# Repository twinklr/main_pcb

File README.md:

# Twinklr Main Board

This repository contains layouts for the Twinklr main PCB in EAGLE's `brd` and `sch` formats. Gerber files are also included.

## `twinklr_board`

This was the original Twinklr board with a built-in 1W amplifier. Unfortunately, it doesn't really work very well, so the amplifier was removed from the final version.

## `twinklr_board_5v`

This is the board used in the current version of Twinklr. It distributes 5V from a tip-negative PSU to the Raspberry Pi, rather than stepping down 9V with a regulator. It has no amplifier.

## License  

Twinklr is Open Hardware.

<br /><span
xmlns:dct="http://purl.org/dc/terms/" property="dct:title">Twinklr</span> by
<span xmlns:cc="http://creativecommons.org/ns#"
property="cc:attributionName">Tom Armitage and Richard Birkin</span> is Open
Hardware. It is licensed under a <a rel="license"
href="http://creativecommons.org/licenses/by-sa/4.0/">Creative Commons
Attribution-ShareAlike 4.0 International License</a>  
If you use any work in this project, you should credit us, and you must
republish any changes you make under the same license. This license does permit
commercial use of these designs, but consider getting in touch before selling
anything.

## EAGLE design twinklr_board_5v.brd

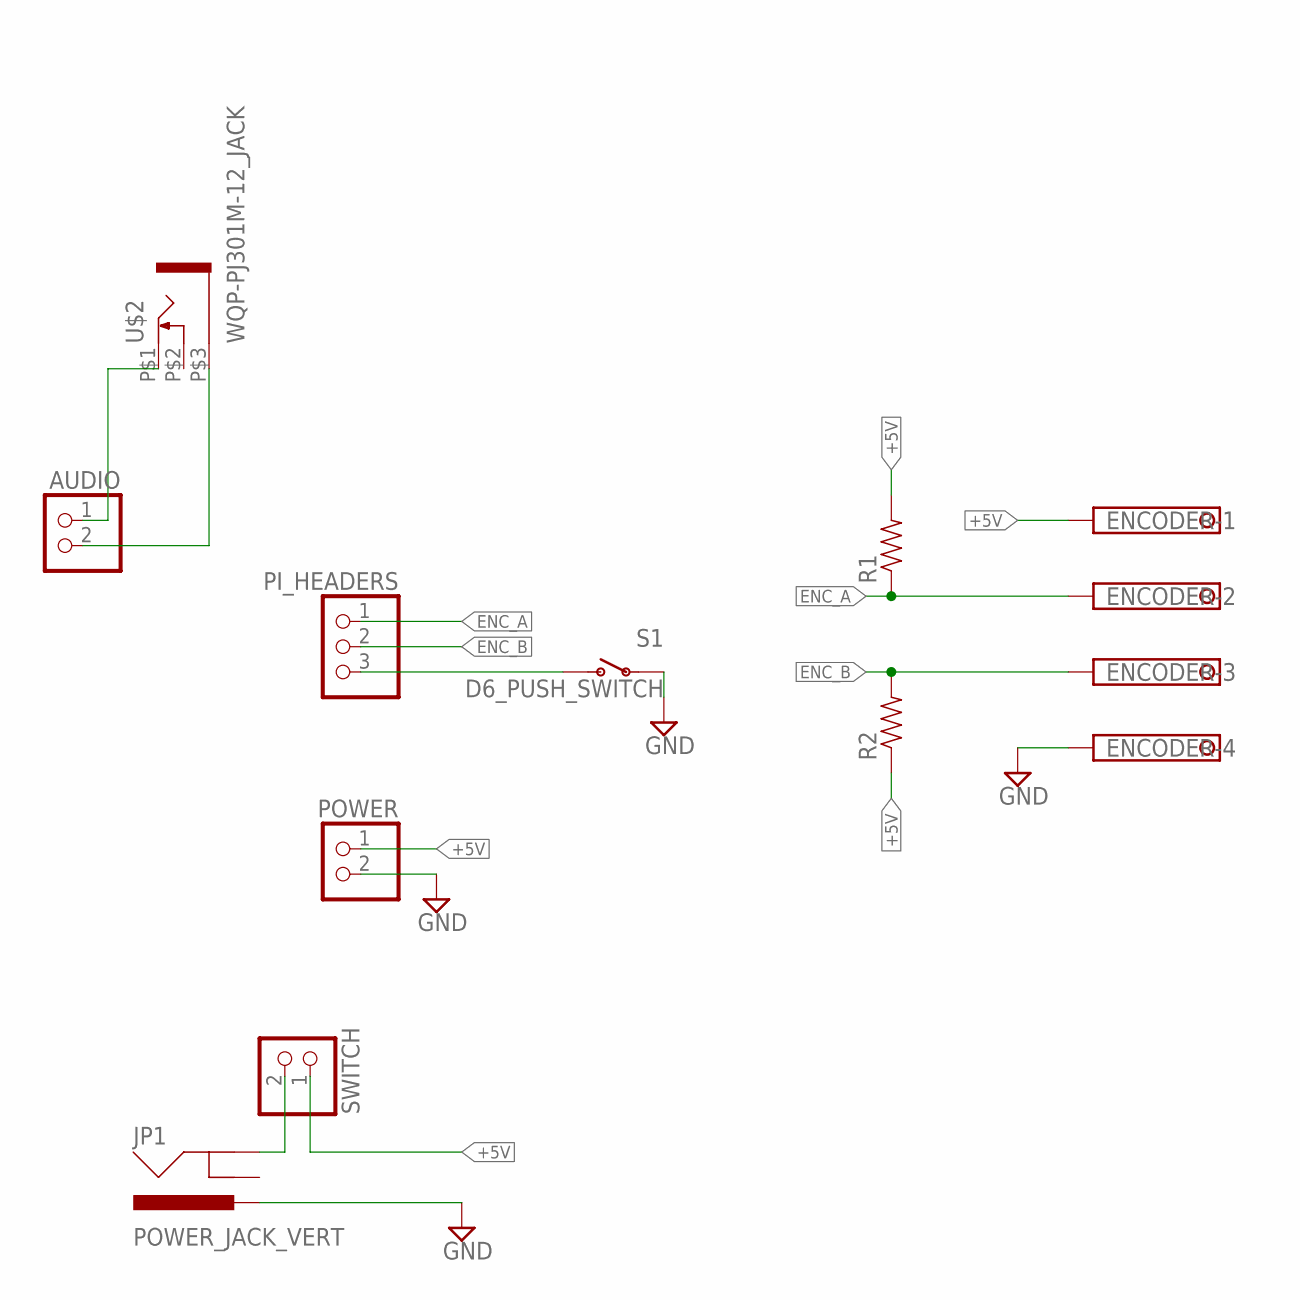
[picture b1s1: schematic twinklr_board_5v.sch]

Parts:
AUDIO: PINHD-1X2; 1X02
ENCODER: 1751264
JP1: POWER_JACK_VERT
PI_HEADERS: PINHD-1X3; 1X03
POWER: PINHD-1X2; 1X02
R1, R2: RESISTORAXIAL-0.3; AXIAL-0.3
S1: D6_PUSH_SWITCH
SWITCH: PINHD-1X2; 1X02
U$2: WQP-PJ301M-12_JACK

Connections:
+5V: ENCODER.1, POWER.1, R1.P$2 (2), R2.P$1 (1), SWITCH.1
ENC_A: ENCODER.2, PI_HEADERS.1, R1.P$1 (1)
ENC_B: ENCODER.3, PI_HEADERS.2, R2.P$2 (2)
GND: ENCODER.4, JP1.PWR, POWER.2, S1.P$3, S1.P$4
unnamed: AUDIO.2, U$2.P$3 (1)
unnamed: AUDIO.1, U$2.P$1 (2)
unnamed: JP1.GND, SWITCH.2
unnamed: PI_HEADERS.3, S1.P$1 (O), S1.P$2 (O)

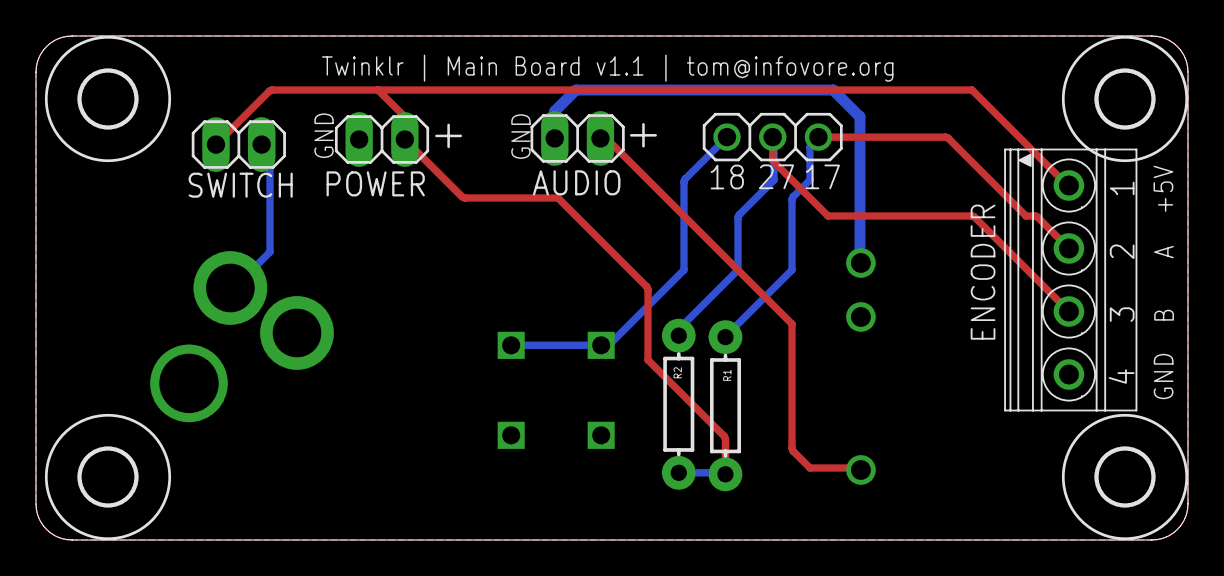
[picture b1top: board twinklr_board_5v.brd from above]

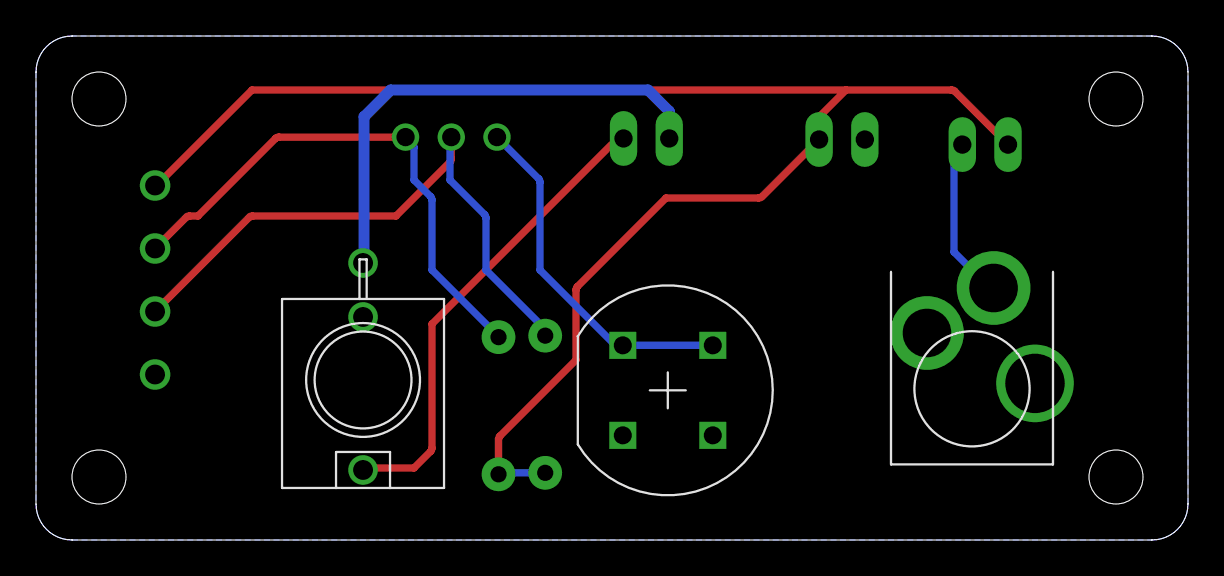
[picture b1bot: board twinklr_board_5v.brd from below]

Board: 2 copper layers, 64.0 x 28.0 mm, 14 parts (3 on the bottom side), 8 nets.

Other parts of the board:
U$1, U$3, U$4, U$5: 3,0

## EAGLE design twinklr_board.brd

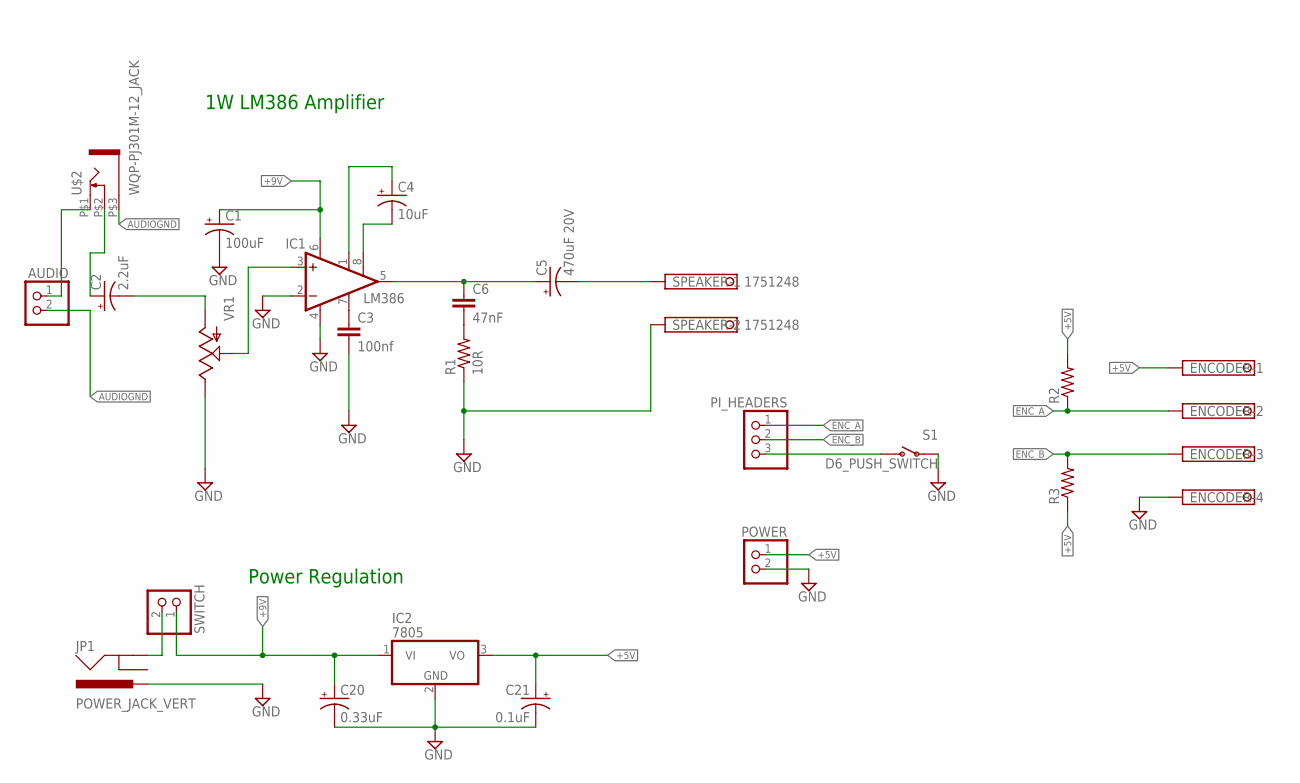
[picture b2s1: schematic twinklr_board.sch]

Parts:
AUDIO: PINHD-1X2; 1X02
C1: 100uF; CPOL-RADIAL-10UF-25V
C2: 2.2uF; CPOL-RADIAL-10UF-25V
C3: 100nf; CAP-PTH-SMALL
C4: 10uF; CPOL-RADIAL-10UF-25V
C5: 470uF 20V; CPOL-RADIAL-1000UF-25V
C6: 47nF; AXIAL-5MM
C20: 0.33uF; CPOL-RADIAL-10UF-25V
C21: 0.1uF; CPOL-RADIAL-10UF-25V
ENCODER: 1751264
IC1: LM386; DIL08
IC2: 7805; TO220V
JP1: POWER_JACK_VERT
PI_HEADERS: PINHD-1X3; 1X03
POWER: PINHD-1X2; 1X02
R1: 10R; AXIAL-0.3
R2, R3: RESISTORAXIAL-0.3; AXIAL-0.3
S1: D6_PUSH_SWITCH
SPEAKER: 1751248
SWITCH: PINHD-1X2; 1X02
U$2: WQP-PJ301M-12_JACK
VR1: POT; ALPS_POT

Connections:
+5V: C21.1 (+), ENCODER.1, IC2.3 (VO), POWER.1, R2.P$2 (2), R3.P$1 (1)
+9V: C1.1 (+), C20.1 (+), IC1.6 (VS), IC2.1 (VI), SWITCH.1
AUDIOGND: AUDIO.2, U$2.P$3 (1)
ENC_A: ENCODER.2, PI_HEADERS.1, R2.P$1 (1)
ENC_B: ENCODER.3, PI_HEADERS.2, R3.P$2 (2)
GND: C1.2 (-), C3.2, C20.2 (-), C21.2 (-), ENCODER.4, IC1.2 (-IN), IC1.4 (GND), IC2.2 (GND), JP1.PWR, POWER.2, R1.P$1 (1), S1.P$3, S1.P$4, SPEAKER.2, VR1.P$1 (E)
unnamed: AUDIO.1, U$2.P$1 (2)
unnamed: C2.2 (-), VR1.P$3 (A)
unnamed: IC1.3 (+IN), VR1.P$2 (S)
unnamed: C4.1 (+), IC1.1 (GAIN)
unnamed: C4.2 (-), IC1.8 (GAIN)
unnamed: C5.+, C6.P$1 (1), IC1.5 (OUT)
unnamed: C2.1 (+), U$2.P$2 (3)
unnamed: C6.P$2 (2), R1.P$2 (2)
unnamed: C5.-, SPEAKER.1
unnamed: C3.1, IC1.7 (BYPASS)
unnamed: JP1.GND, SWITCH.2
unnamed: PI_HEADERS.3, S1.P$1 (O), S1.P$2 (O)

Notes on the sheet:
1W LM386 Amplifier
Power Regulation

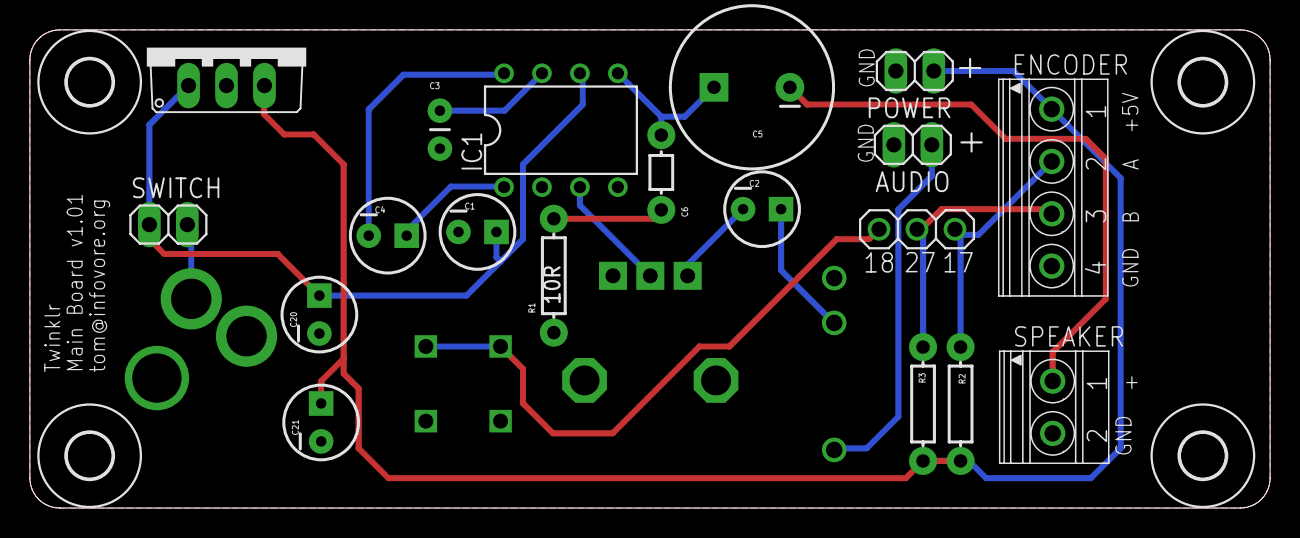
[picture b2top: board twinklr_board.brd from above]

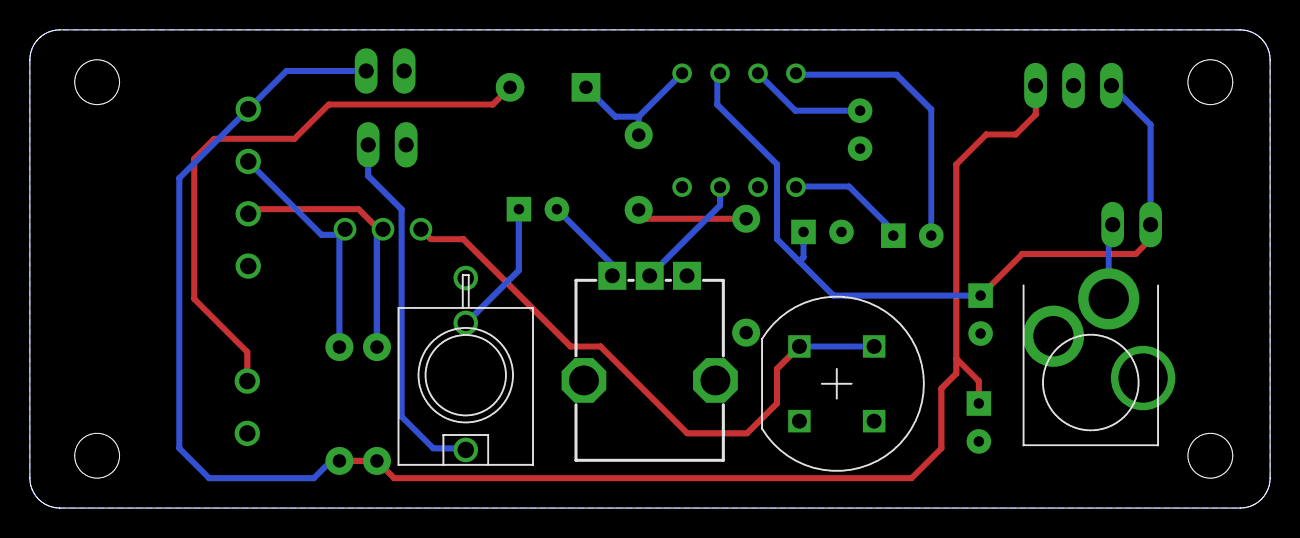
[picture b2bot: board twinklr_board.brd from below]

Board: 2 copper layers, 83.0 x 32.0 mm, 27 parts (4 on the bottom side), 18 nets.

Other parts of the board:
U$1, U$3, U$4, U$5: 3,0

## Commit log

2016-04-25 First commit: work on a rear PCB for Twinklr.
2016-05-10 Making a production board for Ragworm.
2016-05-20 Gerbers for main board.
2016-05-20 README and licensing.
2016-05-27 Yanking out audio ground.
2016-05-27 5V board.
2016-05-27 Ignore EAGLE project files.
2016-05-27 Missed this out.

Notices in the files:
parts and their libraries:
SparkFun-Capacitors: Licensing: Creative Commons ShareAlike 4.0 International - https://creativecommons.org/licenses/by-sa/4.0
